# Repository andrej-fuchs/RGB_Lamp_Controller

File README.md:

RGB Acrylic Lamp Hardware

KiCAD Project and 3D *.step Files

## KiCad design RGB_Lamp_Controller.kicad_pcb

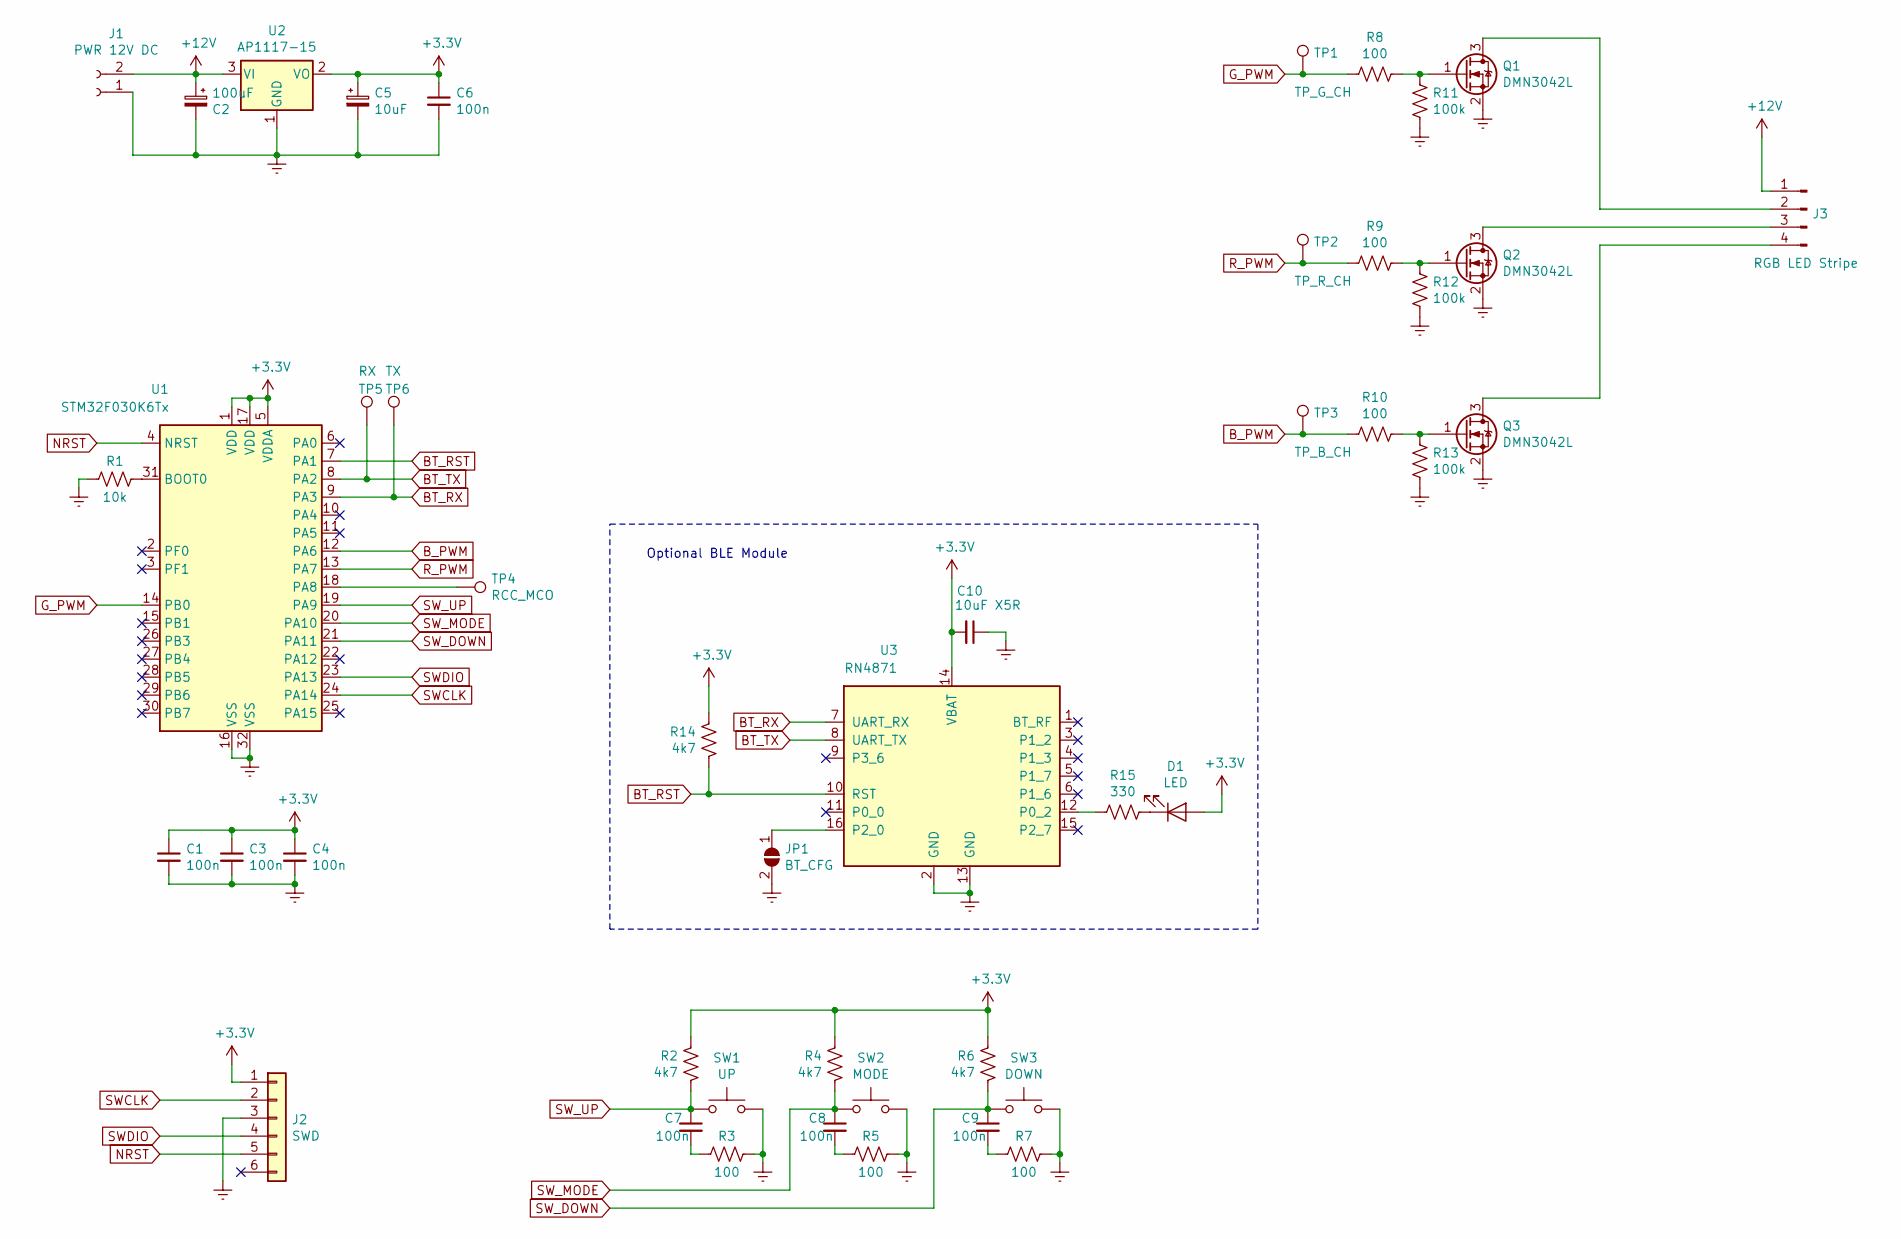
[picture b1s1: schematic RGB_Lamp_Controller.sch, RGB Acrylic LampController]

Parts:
C1, C3, C4, C6, C7, C8, C9: 100n; C_0603_1608Metric_Pad1.05x0.95mm_HandSolder
C2: 100uF; CP_Elec_6.3x5.4
C5: 10uF; CP_Elec_6.3x5.4
C10: 10uF X5R; C_0603_1608Metric_Pad1.05x0.95mm_HandSolder
D1: LED; LED_0805_2012Metric
J1: PWR 12V DC; PWR-Terminal-Pad
J2: SWD; PinHeader_1x06_P2.54mm_Vertical
J3: RGB LED Stripe; RGB-LED-Stripe
JP1: BT_CFG; SolderJumper-2_P1.3mm_Open_TrianglePad1.0x1.5mm
Q1, Q2, Q3: DMN3042L; SOT-23
R1: 10k; R_0603_1608Metric
R2, R4, R6, R14: 4k7; R_0603_1608Metric
R3, R5, R7, R8, R9, R10: 100; R_0603_1608Metric
R11, R12, R13: 100k; R_0603_1608Metric
R15: 330; R_0603_1608Metric
SW1: UP; SW_PUSH_6mm_H13mm
SW2: MODE; SW_PUSH_6mm_H13mm
SW3: DOWN; SW_PUSH_6mm_H13mm
TP1: TP_G_CH; TestPoint_THTPad_D1.0mm_Drill0.5mm
TP2: TP_R_CH; TestPoint_THTPad_D1.0mm_Drill0.5mm
TP3: TP_B_CH; TestPoint_THTPad_D1.0mm_Drill0.5mm
TP4: RCC_MCO; TestPoint_THTPad_D1.0mm_Drill0.5mm
TP5: RX; TestPoint_THTPad_D1.0mm_Drill0.5mm
TP6: TX; TestPoint_THTPad_D1.0mm_Drill0.5mm
U1: STM32F030K6Tx; LQFP-32_7x7mm_P0.8mm
U2: AP1117-15; SOT-223-3_TabPin2
U3: RN4871; Microchip_RN4871

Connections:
+3V3: C1.1, C3.1, C4.1, C5.1, C6.1, C10.2, D1.2 (A), J2.1, R2.2, R4.2, R6.2, R14.2, U1.1 (VDD), U1.5 (VDDA), U1.17 (VDD), U2.2 (VO), U3.14 (VBAT)
+12V: C2.1, J1.2, J3.1, U2.3 (VI)
BT_RST: R14.1, U1.7 (PA1), U3.10 (RST)
BT_RX: TP6.1, U1.9 (PA3), U3.7 (UART_RX)
BT_TX: TP5.1, U1.8 (PA2), U3.8 (UART_TX)
B_PWM: R10.2, TP3.1, U1.12 (PA6)
Earth: C1.2, C2.2, C3.2, C4.2, C5.2, C6.2, C10.1, J1.1, J2.3, JP1.2 (B), Q1.2 (S), Q2.2 (S), Q3.2 (S), R1.2, R3.1, R5.1, R7.1, R11.2, R12.2, R13.2, SW1.2, SW2.2, SW3.2, U1.16 (VSS), U1.32 (VSS), U2.1 (GND), U3.2 (GND), U3.13 (GND)
G_PWM: R8.2, TP1.1, U1.14 (PB0)
NRST: J2.5, U1.4 (NRST)
unnamed: C7.2, R3.2
unnamed: C8.2, R5.2
unnamed: C9.2, R7.2
unnamed: D1.1 (K), R15.1
unnamed: J3.2, Q1.3 (D)
unnamed: J3.3, Q2.3 (D)
unnamed: J3.4, Q3.3 (D)
unnamed: JP1.1 (A), U3.16 (P2_0)
unnamed: Q1.1 (G), R8.1, R11.1
unnamed: Q2.1 (G), R9.1, R12.1
unnamed: Q3.1 (G), R10.1, R13.1
unnamed: R1.1, U1.31 (BOOT0)
unnamed: R15.2, U3.12 (P0_2)
unnamed: TP4.1, U1.18 (PA8)
R_PWM: R9.2, TP2.1, U1.13 (PA7)
SWCLK: J2.2, U1.24 (PA14)
SWDIO: J2.4, U1.23 (PA13)
SW_DOWN: C9.1, R6.1, SW3.1, U1.21 (PA11)
SW_MODE: C8.1, R4.1, SW2.1, U1.20 (PA10)
SW_UP: C7.1, R2.1, SW1.1, U1.19 (PA9)

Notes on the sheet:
Optional BLE Module

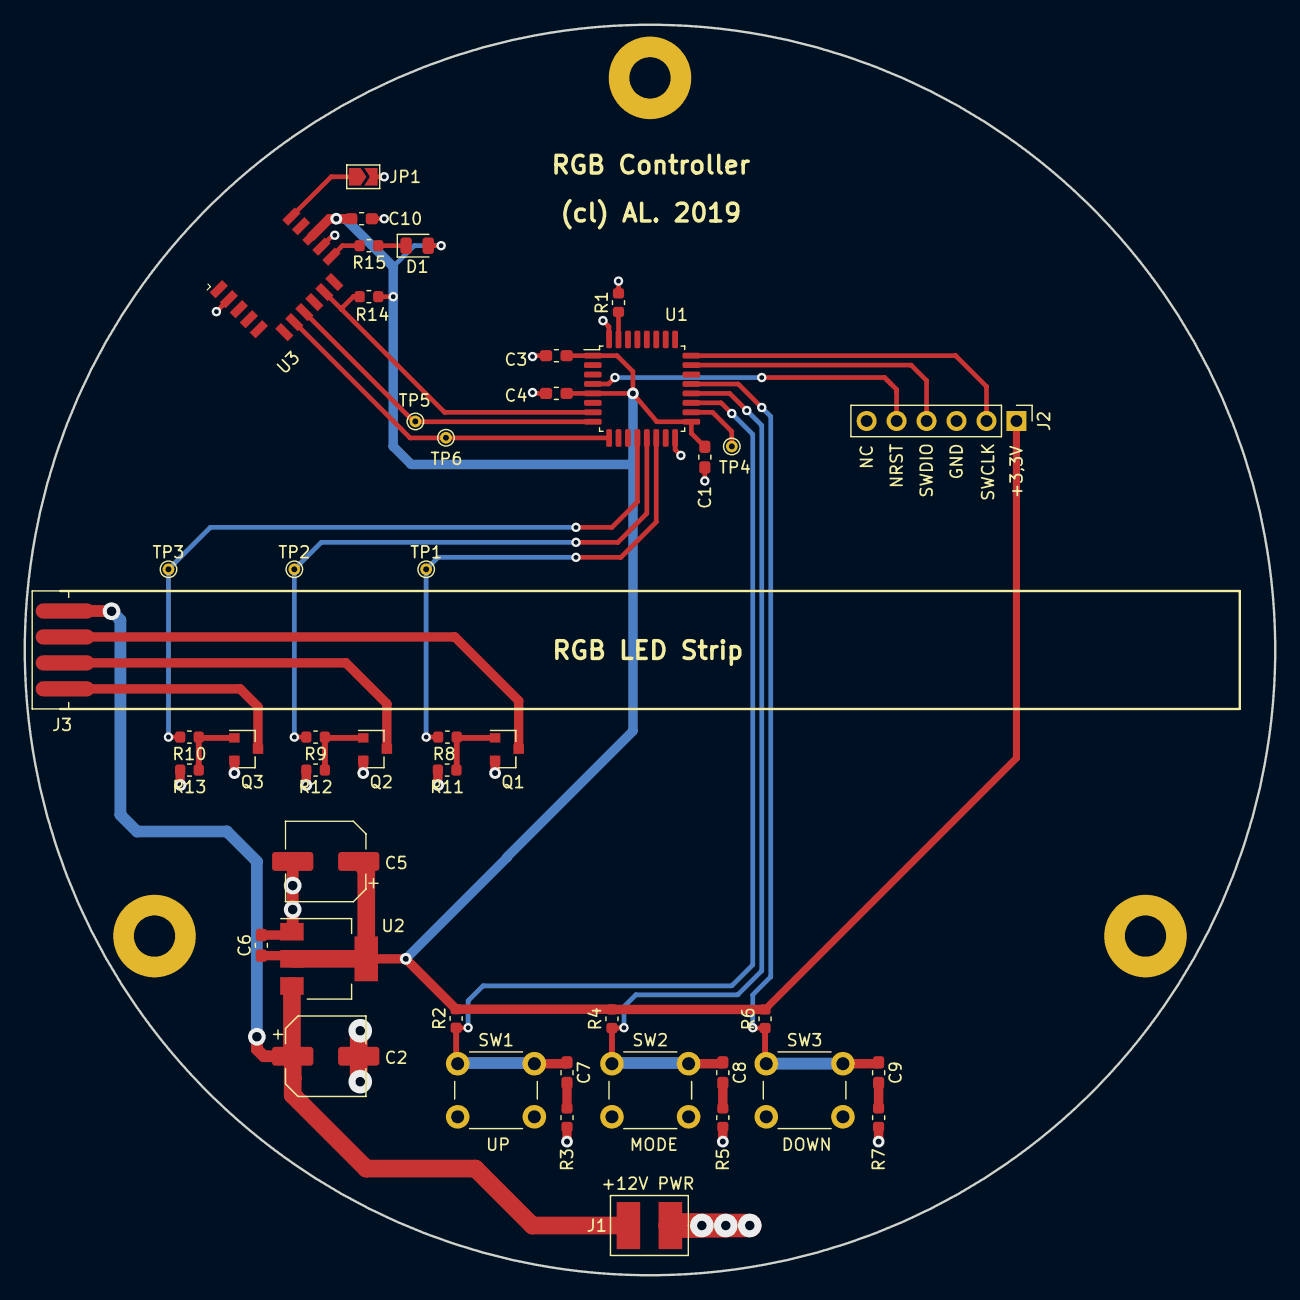
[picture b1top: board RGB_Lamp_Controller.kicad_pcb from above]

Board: 2 copper layers, 106.0 x 106.0 mm, 45 parts (0 on the bottom side), 29 nets.

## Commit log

2020-12-27 Add Readme
2020-12-27 deleted *.bak files
2020-12-27 add images
